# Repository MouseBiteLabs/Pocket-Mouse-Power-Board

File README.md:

# Pocket Mouse Power Board

This is a power regulator board for my <a href="https://github.com/MouseBiteLabs/Game-Boy-Pocket-Color">Game Boy Pocket Color (MGBC)</a> project. This *should* work perfectly fine on a regular Game Boy Color or Pocket, but I haven't exhaustively tested it yet. I have, however, tested it in my MGBC project extensively.

Please note I developed this board for use with the MGBC with NiMH AAA batteries. If you use this power board on the MGBC, your experience with alkaline AAAs may vary. See the section below the BOM for information on improving the experience with alkaline batteries.

*Note: Image of assembled board shows v1.2, rather than the current v1.3. The differences are minimal - see details below.*

## Disclaimer

I highly suggest testing this board before installation in a Game Boy. Failure to do so may result in an irreversibly damaged Game Boy. See the testing sequence below.

**This is a complicated build that requires high level soldering skills. Please do not attempt if you do not have advanced soldering experience. Do not attempt to hand-solder the QFN component on this board, you must use either hot air or a hot plate. I am not responsible for any damage done to you or your Game Boy. You accept any and all risks associated with attempting this project.**

## Board Characteristics and Order Information

The zipped folder contains all the gerber files for this board.
-	Layers: 2
-	Thickness: 1.6mm or thinner
-	Surface Finish: ENIG or HASL (ENIG may be easier to solder)

**I sell this board on Etsy, so you don't have to buy multiples from board fabricators:**

You can alternatively use the zipped folder at any board fabricator you like. You may also buy the board from PCBWay using this link (disclosure: I receive 10% of the sale value to go towards future PCB orders):

And finally, insideGadgets sells these boards fully populated!

## Features

Some features of this power board include: 

* Changing the power switch to a "soft power switch," meaning the main power of the Game Boy does not flow through the switch. A dirty power switch can severly impact performance, so using this scheme can remedy that issue.
* Generally improved efficiency over the OEM regulator, and increased switching frequency.
* Bootloop protection circuitry to prevent overdischarge of AAA batteries, and to allow the Game Boy to die gracefully instead of violently stuttering until the regulator gives up.

I generally recommend using rechargeable NiMH batteries with this board, over alkaline batteries. <a href="https://www.amazon.com/Panasonic-BK-4HCCA8BA-eneloop-Pre-Charged-Rechargeable/dp/B00JHKSL0A/ref=sr_1_1_pp?keywords=eneloop%2BAAA&qid=1690853200&sr=8-1&th=1">Here's a listing for the eneloop pro batteries I use in all of my Game Boys.</a> Other brands of rechargeable batteries I have seen used are Ikea LADDA batteries, and Jugee batteries.

## Testing

I suggest testing the assembled board externally before mounting it to your Game Boy. If you have misassembled it, a part is incorrect, if there is a hidden solder bridge, or one of many other issues - your 5 V supply might be too high when you turn it on! This is not ideal for your Game Boy! So, please, test the board before you fully connect it to the system.

### Version 1.3 Testing
- Connect pin 3 (white box) to negative side of the input voltage source - such as a battery holder with alligator clips or a benchtop power supply.
- Connect pins 1 and 2 (red and yellow boxes) to positive side of the input voltage source. The voltage from the power source must be at least 2.2 V (do not exceed ~4.5 V).
- Turn power on.
- Measure voltage using a multimeter in DC voltage mode - positive probe on pin 7 (blue box) and negative probe on pin 3 (white box). The voltage should read between 4.95 V and 5.05 V.

If your board does not turn on, check orientation of D1 (and other components).

### Version 1.2 Testing
- Connect pin 3 (white box) to negative side of the input voltage source - such as a battery holder with alligator clips or a benchtop power supply.
- Connect pin 2 (yellow box) to positive side of the input voltage source. The voltage from the power source must be at least 2.2 V (do not exceed ~4.5 V).
- Turn power on. Wait 10 seconds for capacitors to fully charge.
- Connect pin 1 (red box) to pin 2 (yellow box) using a switch (preferred) or some other means, such as a wire.
- Measure voltage using a multimeter in DC voltage mode - positive probe on pin 7 (blue box) and negative probe on pin 3 (white box). The voltage should read between 4.95 V and 5.05 V.

### Safely Testing Any Version Using a Game Boy
- Connect pins 1 (red box), 2 (yellow box), and 3 (white box) to the proper locations on the Game Boy circuit board using wire. DO NOT CONNECT PIN 7 (blue box)!!
- Connect input voltage source to the battery tabs (battery holder with alligator clips, power supply, or simply putting the board in the back half of a Game Boy shell with batteries). Voltage source must be at least 2.2 V (do not exceed ~4.5 V).
- Turn the power switch on.
- Measure voltage using a multimeter in DC voltage mode - positive probe on pin 7 (blue box) and negative probe on pin 3 (white box). The voltage should read between 4.95 V and 5.05 V.

## Using with a Game Boy Color or Game Boy Pocket

*Note: This board only supplies the 5V power rail - there are no LCD supplies. This board is only a proper replacement if you have modded your system with a modern IPS kit.*

If you wish to use this on an original Game Boy system, you must:

* Remove U5 from the Game Boy circuit board (the DC/DC converter board) and replace it with this one. Make sure you have a header pin populated for pin 2 on the socket!
* On the main Game Boy PCB, add a wire from pin 2 of the U5 socket to the node labelled SW1-VCC. This node connects to the power switch and F1, so you can choose either points. Note that Game Boy Pockets do not have pin 2 available, so you must run a wire directly from the Pocket Mouse Power Board's pin 2 instead.
* If you are soldering a wire to the fuse directly, **MAKE SURE YOU CHOOSE THE CORRECT SIDE**. It must be the side that's directly connected to the power switch. A multimeter will not tell you which side of the fuse is which if you have the fuse on the board.

## Bill of Materials

A prepopulated cart from Mouser can be found here: https://www.mouser.com/ProjectManager/ProjectDetail.aspx?AccessID=9fcbf0306d. The quantities in the cart are enough such that there is at least one extra component in case you drop or lose one, except for U1 and U2 as they are more expensive. You may want to consider ordering multiple quantities of those parts just in case.

If parts are out of stock or backordered, you can search for the parts on Digikey. The only parts that have no replacements are U1 and U2, every other component has suitable alternate parts you can search for. 

(Is C1 and C3 out of stock? Try GRM21BR61A476ME15K.)

C2 is removed on v1.3, and D1 is only used on v1.3.

| Reference Designators | Qty | Value/Part Number  | Package | Description      | Comment                                      | Source                                                                                                                                                                                                                                                 |
| --------------------- | --- | ------------------ | ------- | ---------------- | -------------------------------------------- | ------------------------------------------------------------------------------------------------------------------------------------------------------------------------------------------------------------------------------------------------------ |
| C1, C3                | 2   | 47uF               | 0805    | Capacitor (MLCC) | X5R or better, 10V or higher                 | [https://www.mouser.com/ProductDetail/Murata-Electronics/GRM21BR61A476ME15L?qs=hNud%2FORuBR2%2FEB7WUpdltg%3D%3D](https://www.mouser.com/ProductDetail/Murata-Electronics/GRM21BR61A476ME15L?qs=hNud%2FORuBR2%2FEB7WUpdltg%3D%3D)                       |
| C4                    | 1   | 0.1uF              | 0603    | Capacitor (MLCC) | C2 is removed on v1.3                        | [https://www.mouser.com/ProductDetail/KEMET/C0603C104M3RACTU?qs=7q2aiX3Gdlh4qBRaMcnohQ%3D%3D](https://www.mouser.com/ProductDetail/KEMET/C0603C104M3RACTU?qs=7q2aiX3Gdlh4qBRaMcnohQ%3D%3D)                                                             |
| C5                    | 1   | 22uF               | 0805    | Capacitor (MLCC) | X5R or better, 16V or higher                 | [https://www.mouser.com/ProductDetail/Murata-Electronics/GRM21BR61E226ME44K?qs=hNud%2FORuBR25jDsUehWlrQ%3D%3D](https://www.mouser.com/ProductDetail/Murata-Electronics/GRM21BR61E226ME44K?qs=hNud%2FORuBR25jDsUehWlrQ%3D%3D)                           |
| D1                    | 1   | BAT42              | SOD323  | Schottky Diode   | Only used on v1.3                            | https://www.mouser.com/ProductDetail/78-BAT42WS-E3-18                                                                                                                                                                                                  |
| L1                    | 1   | 2.2uH              | 1212    | Inductor         | Saturation current higher than 1 A preferred | https://www.mouser.com/ProductDetail/810-VLS3012HBX2R2M-N                                      |
| Q1                    | 1   | MMBT3906           | SOT23   | PNP BJT          |                                              | [https://www.mouser.com/ProductDetail/Micro-Commercial-Components-MCC/MMBT3906HE3-TP?qs=HBWAp0VN4Rh%2Ft2ZPx%252BV99A%3D%3D](https://www.mouser.com/ProductDetail/Micro-Commercial-Components-MCC/MMBT3906HE3-TP?qs=HBWAp0VN4Rh%2Ft2ZPx%252BV99A%3D%3D) |
| Q2, Q4                | 2   | 2N7002             | SOT23   | N-channel MOSFET |                                              | [https://www.mouser.com/ProductDetail/Nexperia/2N7002NXBKR?qs=%252B6g0mu59x7J2ddJstTJGkQ%3D%3D](https://www.mouser.com/ProductDetail/Nexperia/2N7002NXBKR?qs=%252B6g0mu59x7J2ddJstTJGkQ%3D%3D)                                                         |
| Q3                    | 1   | MMBT3904           | SOT23   | NPN BJT          |                                              | [https://www.mouser.com/ProductDetail/Nexperia/MMBT3904VL?qs=cnAQGvEIVkKbCwIpHJoHxQ%3D%3D](https://www.mouser.com/ProductDetail/Nexperia/MMBT3904VL?qs=cnAQGvEIVkKbCwIpHJoHxQ%3D%3D)                                                                   |
| R1, R4, R8            | 3   | 100k               | 0603    | Resistor         |                                              | [https://www.mouser.com/ProductDetail/YAGEO/RC0603FR-07100KL?qs=e1ok2LiJcmaihem8Va5%2Fsw%3D%3D](https://www.mouser.com/ProductDetail/YAGEO/RC0603FR-07100KL?qs=e1ok2LiJcmaihem8Va5%2Fsw%3D%3D)                                                         |
| R2, R3, R5            | 3   | 10k                | 0603    | Resistor         |                                              | [https://www.mouser.com/ProductDetail/YAGEO/RC0603FR-0710KL?qs=grNVn54RoB%252B3GtjbJj3wJQ%3D%3D](https://www.mouser.com/ProductDetail/YAGEO/RC0603FR-0710KL?qs=grNVn54RoB%252B3GtjbJj3wJQ%3D%3D)                                                       |
| R6                    | 1   | 47k                | 0603    | Resistor         |                                              | [https://www.mouser.com/ProductDetail/YAGEO/RC0603FR-0747KL?qs=gt6vzsuosg3jXzmCiDCCdg%3D%3D](https://www.mouser.com/ProductDetail/YAGEO/RC0603FR-0747KL?qs=gt6vzsuosg3jXzmCiDCCdg%3D%3D)                                                               |
| U1                    | 1   | TPS61202           | VSON-10 | Boost Converter  |                                              | [https://www.mouser.com/ProductDetail/Texas-Instruments/TPS61202DRCR?qs=KS%252B%252BetD%2FUt9ba9GgZBolfg%3D%3D](https://www.mouser.com/ProductDetail/Texas-Instruments/TPS61202DRCR?qs=KS%252B%252BetD%2FUt9ba9GgZBolfg%3D%3D)                         |
| U2                    | 1   | TPS3840DL20        | SOT23-5 | Supervisory IC   |                                              | [https://www.mouser.com/ProductDetail/Texas-Instruments/TPS3840DL20DBVR?qs=T3oQrply3y%2FZsfSrLIG7Ww%3D%3D](https://www.mouser.com/ProductDetail/Texas-Instruments/TPS3840DL20DBVR?qs=T3oQrply3y%2FZsfSrLIG7Ww%3D%3D)                                   |
| --                    | 1   | 10129378-904001BLF | --      | 1x4 Header Pins  |                                              | [https://www.mouser.com/ProductDetail/649-1012937890401BLF](https://www.mouser.com/ProductDetail/649-1012937890401BLF)                                                                                                                                 |
| --                    | 1   | 10129378-903001BLF | --      | 1x3 Header Pins  |                                              | [https://www.mouser.com/ProductDetail/649-1012937890301BLF](https://www.mouser.com/ProductDetail/649-1012937890301BLF)                                                                                                                                 |

## Minimized Parts List and/or for use with Alkaline AAAs

If you don't want the undervoltage lockout mechanism, which may be specifically desirable with alkaline AAAs, you can assemble the board without the following components:
- Capacitor: C1
- Diode: D1
- Resistors: R1, R2, R3, R4, R6
- Transistors: Q1, Q2, Q3, Q4
- IC: U2

If you have built the system, but find alkaline batteries don't last as long as you would expect, you can simply remove U2 and keep everything else on the board to achieve the same effect.

## Potential Issues

- If you use AAA alkaline batteries (for Game Boy Pocket or Pocket Color), you may find that after using them for a few hours (or if you use mismatched batteries), the Game Boy might stutter a bit when turning the power switch on, taking a few seconds to fully turn on. This is likely due to a higher internal resistance of alkaline batteries as they've been discharged, compared to rechargeable NiMH batteries. I generally recommend using rechargeable NiMH AAA batteries over alkalines to avoid this issue. If you are a huge fan of alkaline batteries, you can remove U2 to "extend" the life of the system and prevent the struggling start-up on alkaline batteries.
- Using a flash cart, such as the Everdrive or EZ-Flash, the power draw during start-up may be too high and cause the battery voltage to drop below the 2V threshold. You may be able to get it to boot by turning the power switch off and on again. Regardless, this should only occur when you have very low battery life. The components I have chosen should effectively prevent this error from occurring, but I have not tested every system configuration possible.
- **Version 1.2 only:** When first placing batteries in, you must wait a few seconds for the capacitors to charge up, before it will operate correctly. This is only upon first insertion - once the batteries have been in the system for longer than a few seconds, it will operate completely normally.

## Revision History

### v1.3
- Added diode to fast charge C1 (removes need to wait a few seconds before use after placing batteries in the first time)
- Added test points for various nets
- Removed C2

### v1.2
- Changed C1 to 0805 size
- Added test points for U2 supply voltage and PSU_EN net

### v1.1
- Removed some unnecessary components
- Changed the voltage cut-off to 2V instead of 1.8V to enable reliable bootloop prevention

### v1.0
- Release version

## License
<br />This work is licensed under a <a rel="license" href="http://creativecommons.org/licenses/by-sa/4.0/">Creative Commons Attribution-ShareAlike 4.0 International License</a>. You are able to copy and redistribute the material in any medium or format, as well as remix, transform, or build upon the material for any purpose (even commercial) - but you **must** give appropriate credit, provide a link to the license, and indicate if any changes were made.

©MouseBiteLabs 2023

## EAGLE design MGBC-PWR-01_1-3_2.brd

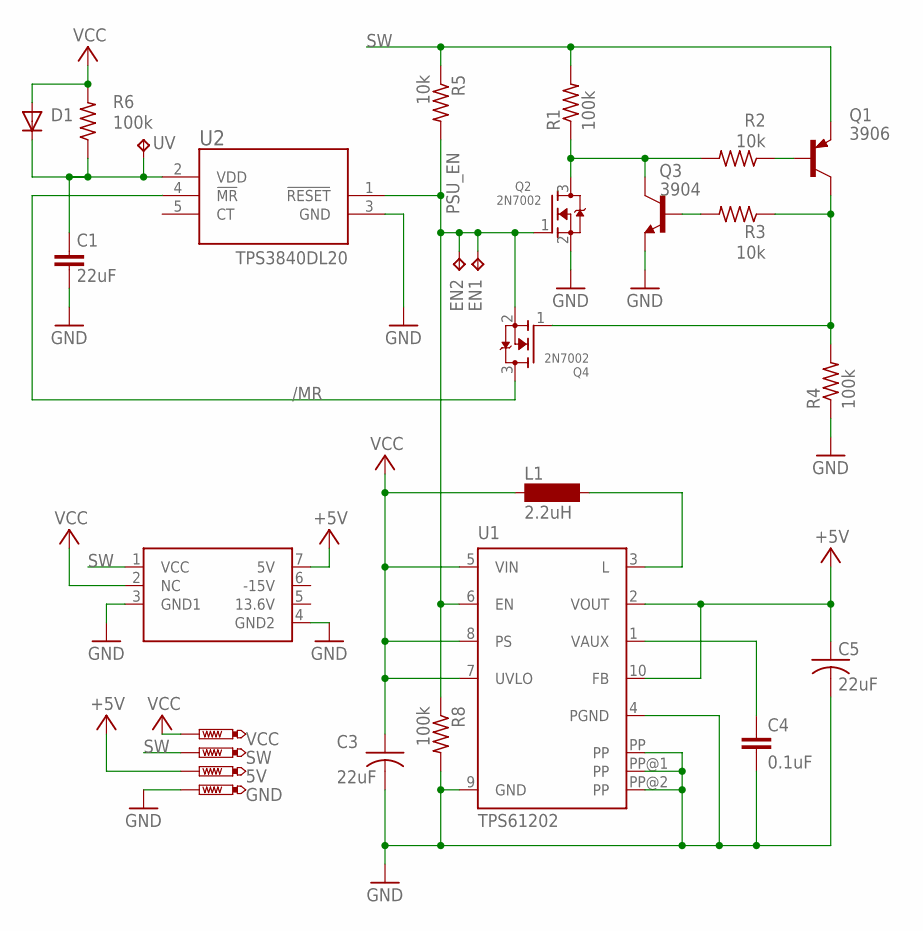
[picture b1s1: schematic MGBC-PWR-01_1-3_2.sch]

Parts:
5V: PTR1B1,27; B1,27
C1, C3, C5: 22uF; C0805
C4: 0.1uF; C0603
D1: DIODESOD-323F; SOD-323F
EN1: TPTP09R; TP09R
EN2: TPB1,27; B1,27
GND: PTR1B1,27; B1,27
L1: 2.2uH; 1212
Q1: MMBT3906LT1SMD; SOT23-BEC
Q2, Q4: 2N7002; SOT23
Q3: 3904; SOT23-BEC
R1, R4, R6, R8: 100k; R0603
R2, R3, R5: 10k; R0603
SW: PTR1B1,27; B1,27
U1: TPS61202; S-PDSO-N10
U2: TPS3840; SOT-23-5
U$1: MGB-PWR_BD; MGB-PWRBD
UV: TPB1,27; B1,27
VCC: PTR1B1,27; B1,27

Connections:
13.6V: U$1.5 (13.6V)
+5V: 5V.TP, C5.1, U1.2 (VOUT), U1.10 (FB), U$1.7 (5V)
-15V: U$1.6 (-15V)
/MR: Q4.3 (D), U2.4 (!MR)
GND: C1.2, C3.2, C4.2, C5.2, GND.TP, Q2.2 (S), Q3.E, R4.1, R8.2, U1.4 (PGND), U1.9 (GND), U1.PP, U1.PP@1 (PP), U1.PP@2 (PP), U2.3 (GND), U$1.3 (GND1), U$1.4 (GND2)
unnamed: C1.1, D1.C, R6.1, U2.2 (VDD), UV.TP
unnamed: Q1.B, R2.1
unnamed: Q1.C, Q4.1 (G), R3.1, R4.2
unnamed: Q3.B, R3.2
unnamed: Q2.3 (D), Q3.C, R1.1, R2.2
unnamed: L1.2, U1.3 (L)
unnamed: C4.1, U1.1 (VAUX)
PSU_EN: EN1.TP, EN2.TP, Q2.1 (G), Q4.2 (S), R5.2, R8.1, U1.6 (EN), U2.1 (!RESET)
SW: Q1.E, R1.2, R5.1, SW.TP, U$1.1 (VCC)
VCC: C3.1, D1.A, L1.1, R6.2, U1.5 (VIN), U1.7 (UVLO), U1.8 (PS), U$1.2 (NC), VCC.TP

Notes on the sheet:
3906
TPS3840DL20

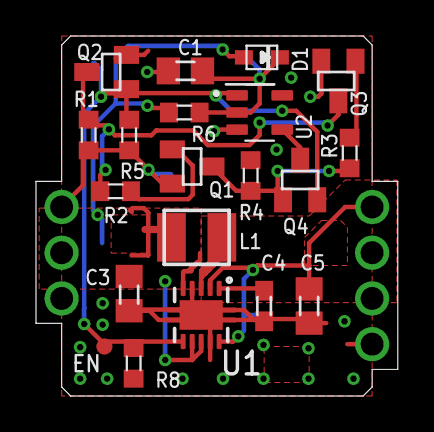
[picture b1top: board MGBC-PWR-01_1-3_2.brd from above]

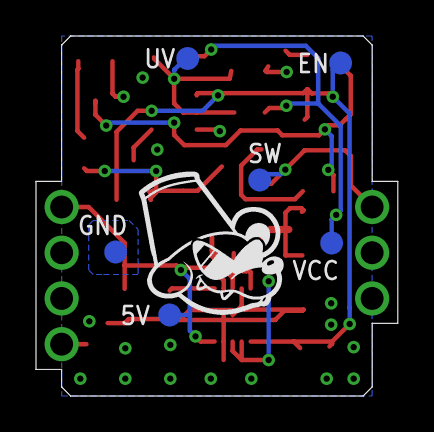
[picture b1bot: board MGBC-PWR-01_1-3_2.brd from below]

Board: 2 copper layers, 20.1 x 20.0 mm, 27 parts (6 on the bottom side), 13 nets.

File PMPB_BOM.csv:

,,,,,Cart link:,https://www.mouser.com/ProjectManager/ProjectDetail.aspx?Acc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
Reference Designators,Qty,Value/Part Number,Package,Description,Comment,Source
"C1, C3",2,47uF,0805,Capacitor (MLCC),"X5R or better, 10V or higher",https://www.mouser.com/ProductDetail/Murata-Electronics/GRM2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
C4,1,0.1uF,0603,Capacitor (MLCC),C2 is removed on v1.3,"	https://www.mouser.com/ProductDetail/KEMET/C0603C104M3RACTU?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"
C5,1,22uF,0805,Capacitor (MLCC),"X5R or better, 16V or higher",https://www.mouser.com/ProductDetail/Murata-Electronics/GRM2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
D1,1,BAT42,SOD323,Schottky Diode,Only used on v1.3,https://www.mouser.com/ProductDetail/78-BAT42WS-E3-18
L1,1,2.2uH,1212,Inductor,Saturation current higher than 1 A preferred,https://www.mouser.com/ProductDetail/Murata-Electronics/LQH3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
Q1,1,MMBT3906,SOT23,PNP BJT,,https://www.mouser.com/ProductDetail/Micro-Commercial-Compon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
"Q2, Q4",2,2N7002,SOT23,N-channel MOSFET,,https://www.mouser.com/ProductDetail/Nexperia/2N7002NXBKR?qs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
Q3,1,MMBT3904,SOT23,NPN BJT,,https://www.mouser.com/ProductDetail/Nexperia/MMBT3904VL?qs=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
"R1, R4, R8",3,100k,0603,Resistor,,https://www.mouser.com/ProductDetail/YAGEO/RC0603FR-07100KL?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
"R2, R3, R5",3,10k,0603,Resistor,,https://www.mouser.com/ProductDetail/YAGEO/RC0603FR-0710KL?q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
R6,1,47k,0603,Resistor,,https://www.mouser.com/ProductDetail/YAGEO/RC0603FR-0747KL?q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
U1,1,TPS61202,VSON-10,Boost Converter,,https://www.mouser.com/ProductDetail/Texas-Instruments/TPS61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
U2,1,TPS3840DL20,SOT23-5,Supervisory IC,,https://www.mouser.com/ProductDetail/Texas-Instruments/TPS38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
--,1,10129378-904001BLF,--,1x4 Header Pins,,https://www.mouser.com/ProductDetail/649-1012937890401BLF
--,1,10129378-903001BLF,--,1x3 Header Pins,,https://www.mouser.com/ProductDetail/649-1012937890301BLF

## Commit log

2023-04-03 Rename DesignDoc.md to README.md
2023-04-03 Update BOM
2023-04-03 Update BOM and disclaimer
2023-04-03 Update BOM quantities
2023-04-04 Upload board and schematic files
2023-04-04 Upload gerbers
2023-04-12 Added issues section
2023-04-15 Updated to v1.2
2023-04-18 Update cart link
2023-07-18 Add v1.3 information
2023-08-01 Add notes about alkaline batteries
